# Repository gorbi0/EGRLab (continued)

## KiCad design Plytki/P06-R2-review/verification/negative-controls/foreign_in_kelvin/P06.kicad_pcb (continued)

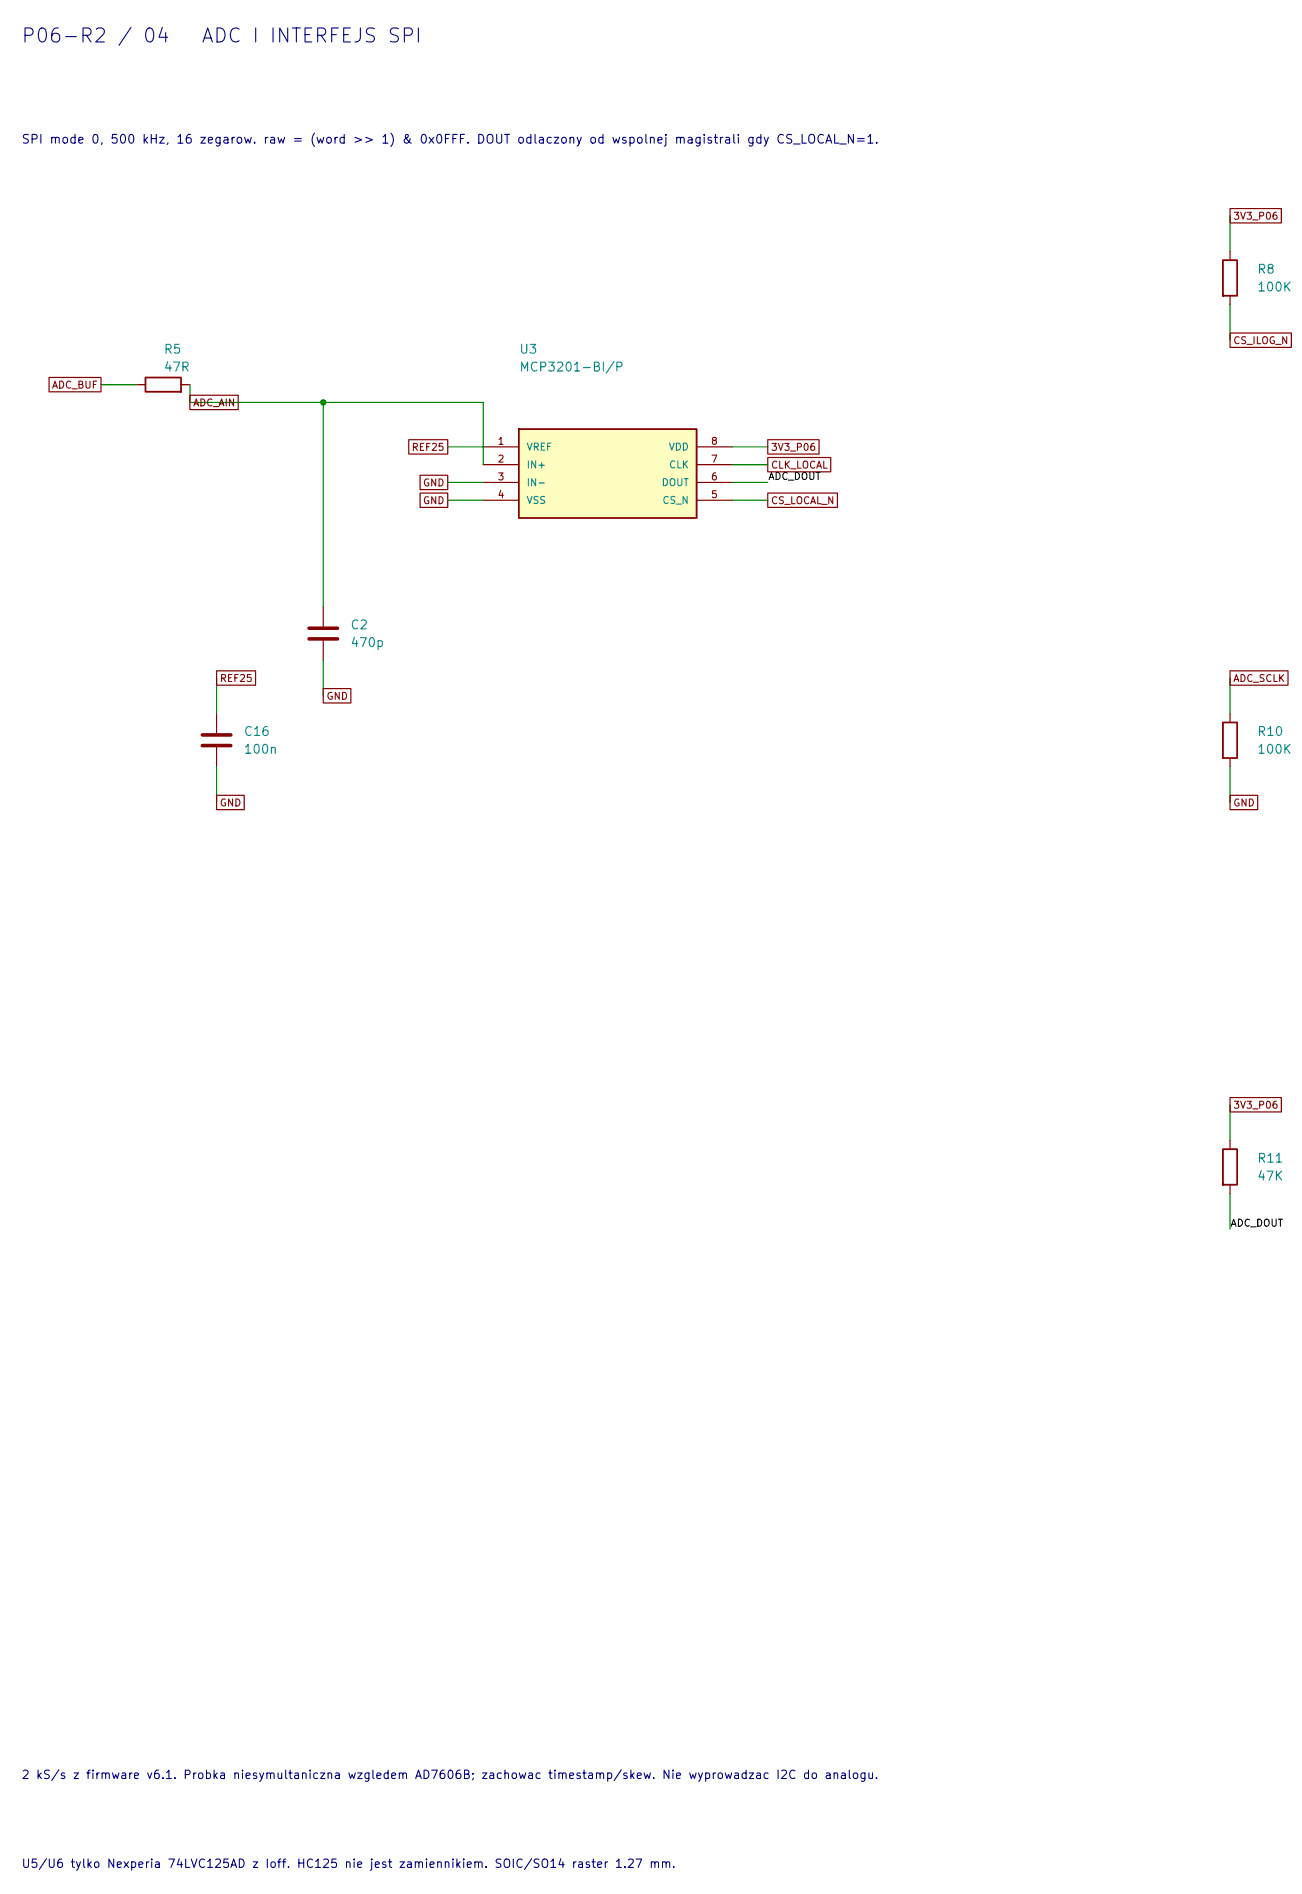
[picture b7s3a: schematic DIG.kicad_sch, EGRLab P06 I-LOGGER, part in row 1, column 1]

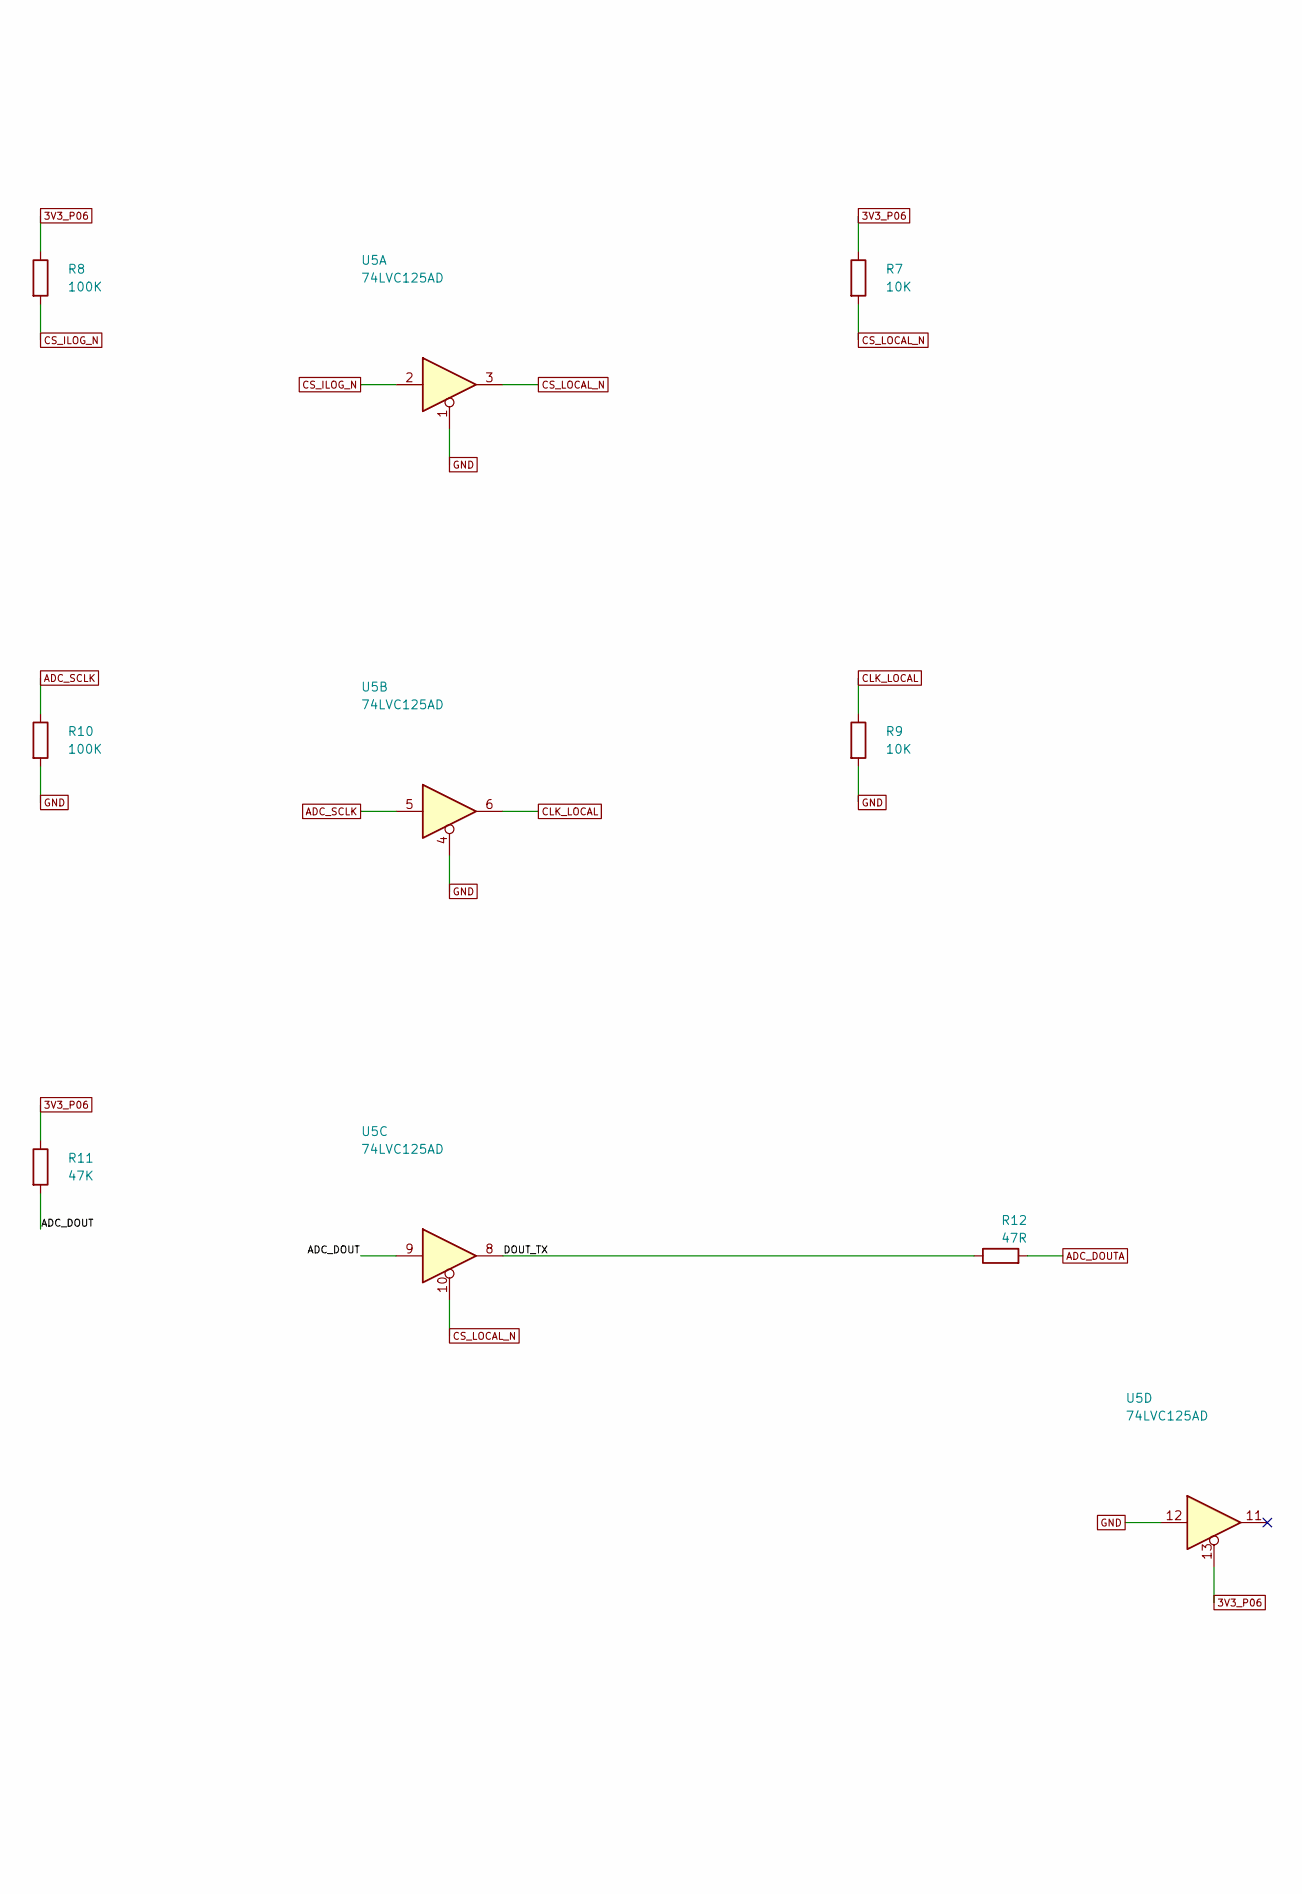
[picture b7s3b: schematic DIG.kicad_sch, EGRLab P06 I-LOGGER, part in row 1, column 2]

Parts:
C2: 470p; C_1206_3216Metric_Pad1.33x1.80mm_HandSolder; MPN SMD 1206 C0G 50V 5% 470p
C16: 100n; C_1206_3216Metric_Pad1.33x1.80mm_HandSolder; MPN SMD 1206 X7R 50V 10% 100n
R5, R12: 47R; R_1206_3216Metric_Pad1.30x1.75mm_HandSolder; MPN RC1206FR-0747RL
R7, R9: 10K; R_1206_3216Metric_Pad1.30x1.75mm_HandSolder; MPN RC1206FR-0710KL
R8, R10: 100K; R_1206_3216Metric_Pad1.30x1.75mm_HandSolder; MPN RC1206FR-07100KL
R11: 47K; R_Axial_DIN0207_L6.3mm_D2.5mm_P5.08mm_Vertical; MPN MF0207FTE-47K (Yageo MF0207 1% 0.6W, ow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
U3: MCP3201-BI/P; DIP-8_W7.62mm; MPN MCP3201-BI/P
U5: 74LVC125AD; SOIC-14_3.9x8.7mm_P1.27mm; MPN 74LVC125AD,118 (Nexperia)

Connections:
3V3_P06: R7.1, R8.1, R11.1, U3.8 (VDD), U5.13; also elsewhere on the board
/DIG/ADC_DOUT: R11.2, U3.6 (DOUT), U5.9
/DIG/DOUT_TX: R12.1, U5.8
ADC_AIN: C2.1, R5.2, U3.2 (IN+); also elsewhere on the board
ADC_BUF: R5.1; also elsewhere on the board
ADC_DOUTA: R12.2; also elsewhere on the board
ADC_SCLK: R10.1, U5.5; also elsewhere on the board
CLK_LOCAL: R9.1, U3.7 (CLK), U5.6; also elsewhere on the board
CS_ILOG_N: R8.2, U5.2; also elsewhere on the board
CS_LOCAL_N: R7.2, U3.5 (CS_N), U5.3, U5.10; also elsewhere on the board
GND: C2.2, C16.2, R9.2, R10.2, U3.3 (IN-), U3.4 (VSS), U5.1, U5.4, U5.12; also elsewhere on the board
REF25: C16.1, U3.1 (VREF); also elsewhere on the board

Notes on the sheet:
SPI mode 0, 500 kHz, 16 zegarow. raw = (word >> 1) & 0x0FFF. DOUT odlaczony od wspolnej magistrali gdy CS_LOCAL_N=1.
2 kS/s z firmware v6.1. Probka niesymultaniczna wzgledem AD7606B; zachowac timestamp/skew. Nie wyprowadzac I2C do analogu.
U5/U6 tylko Nexperia 74LVC125AD z Ioff. HC125 nie jest zamiennikiem. SOIC/SO14 raster 1.27 mm.
P06-R2 / 04 ADC I INTERFEJS SPI

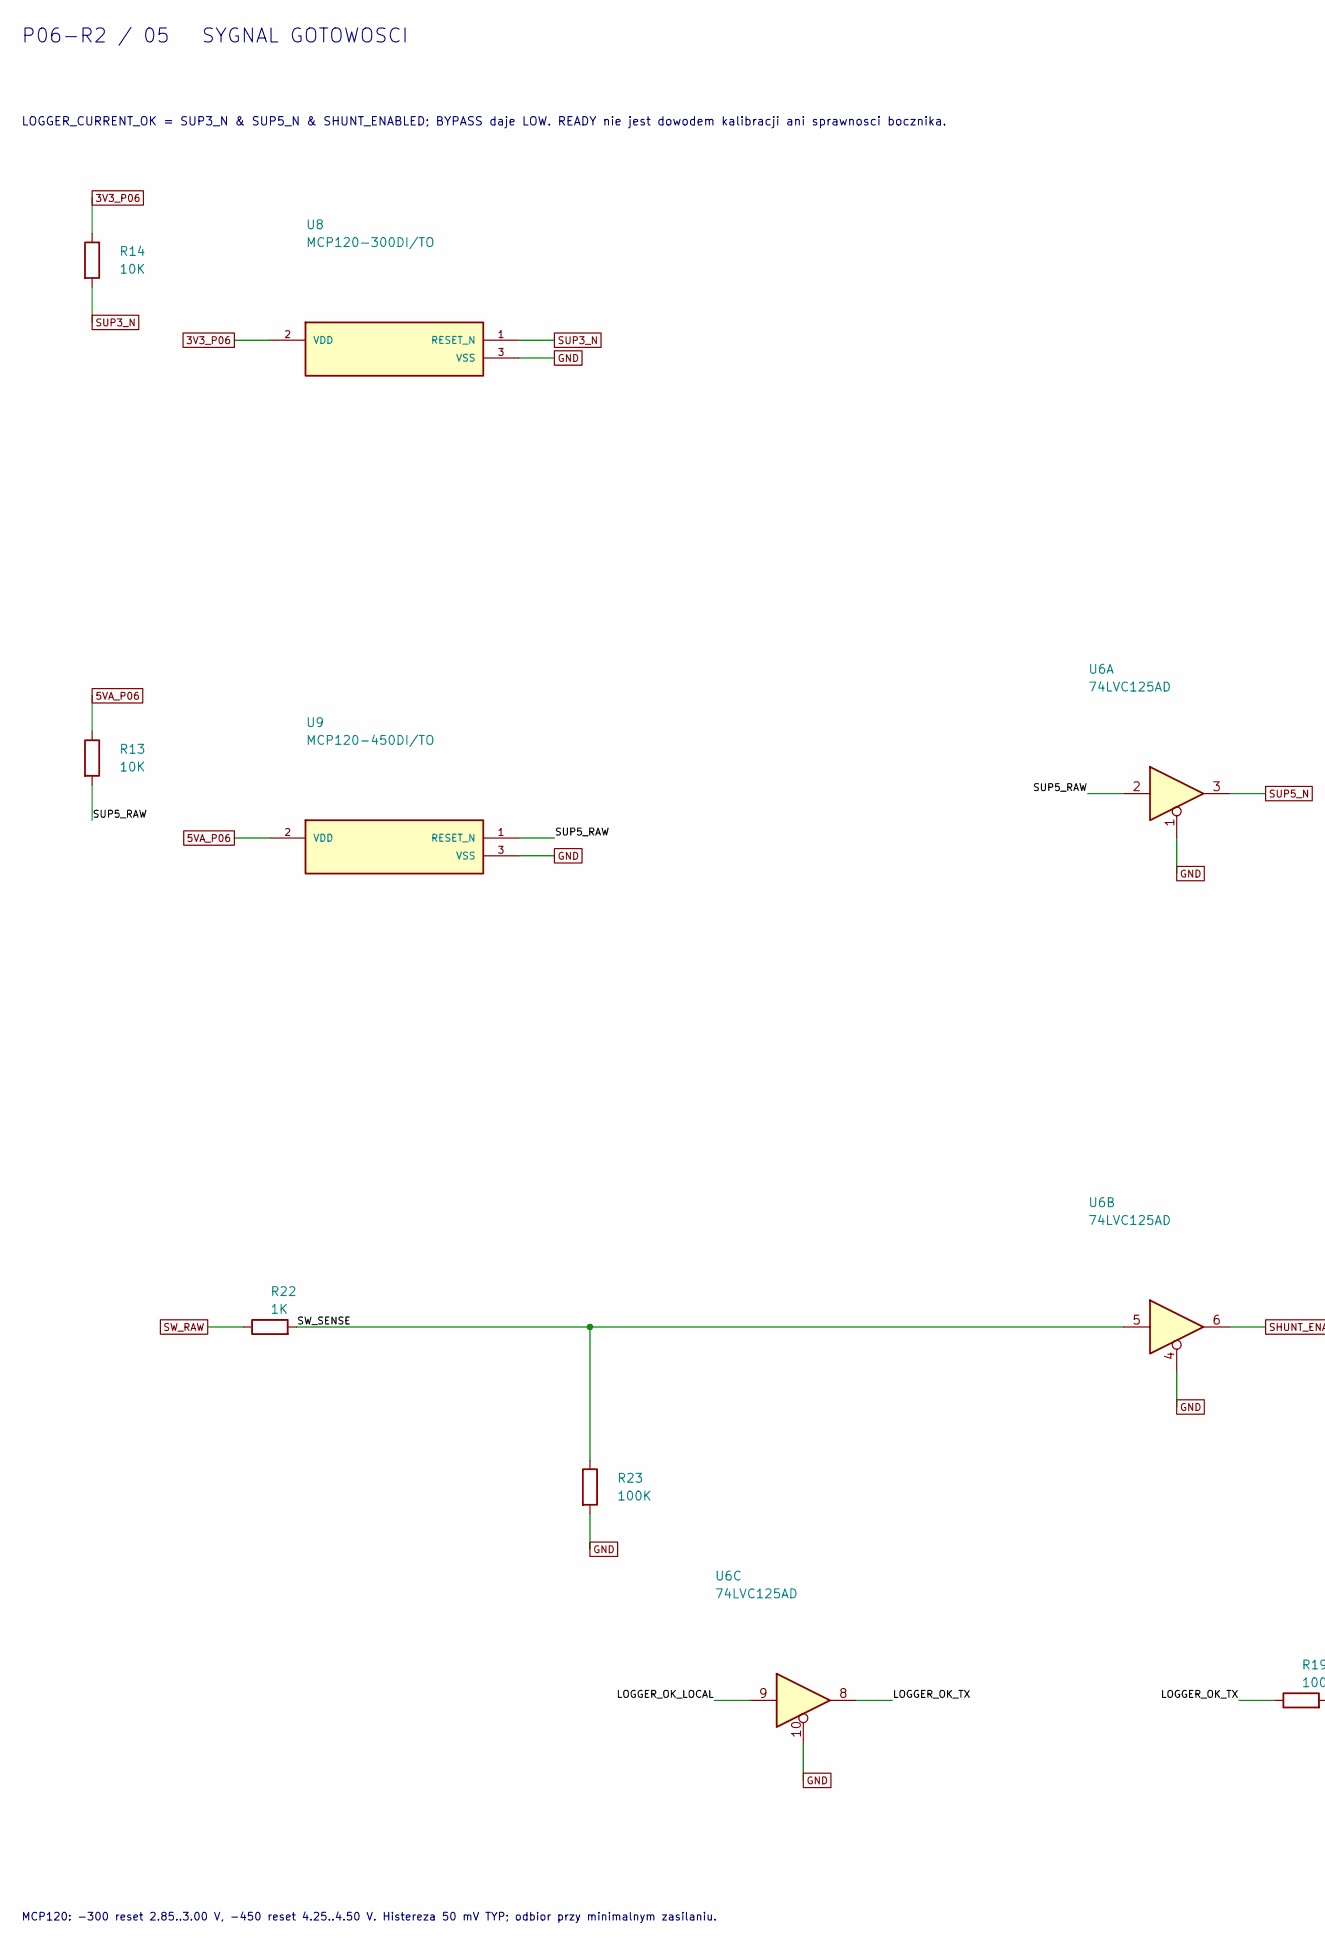
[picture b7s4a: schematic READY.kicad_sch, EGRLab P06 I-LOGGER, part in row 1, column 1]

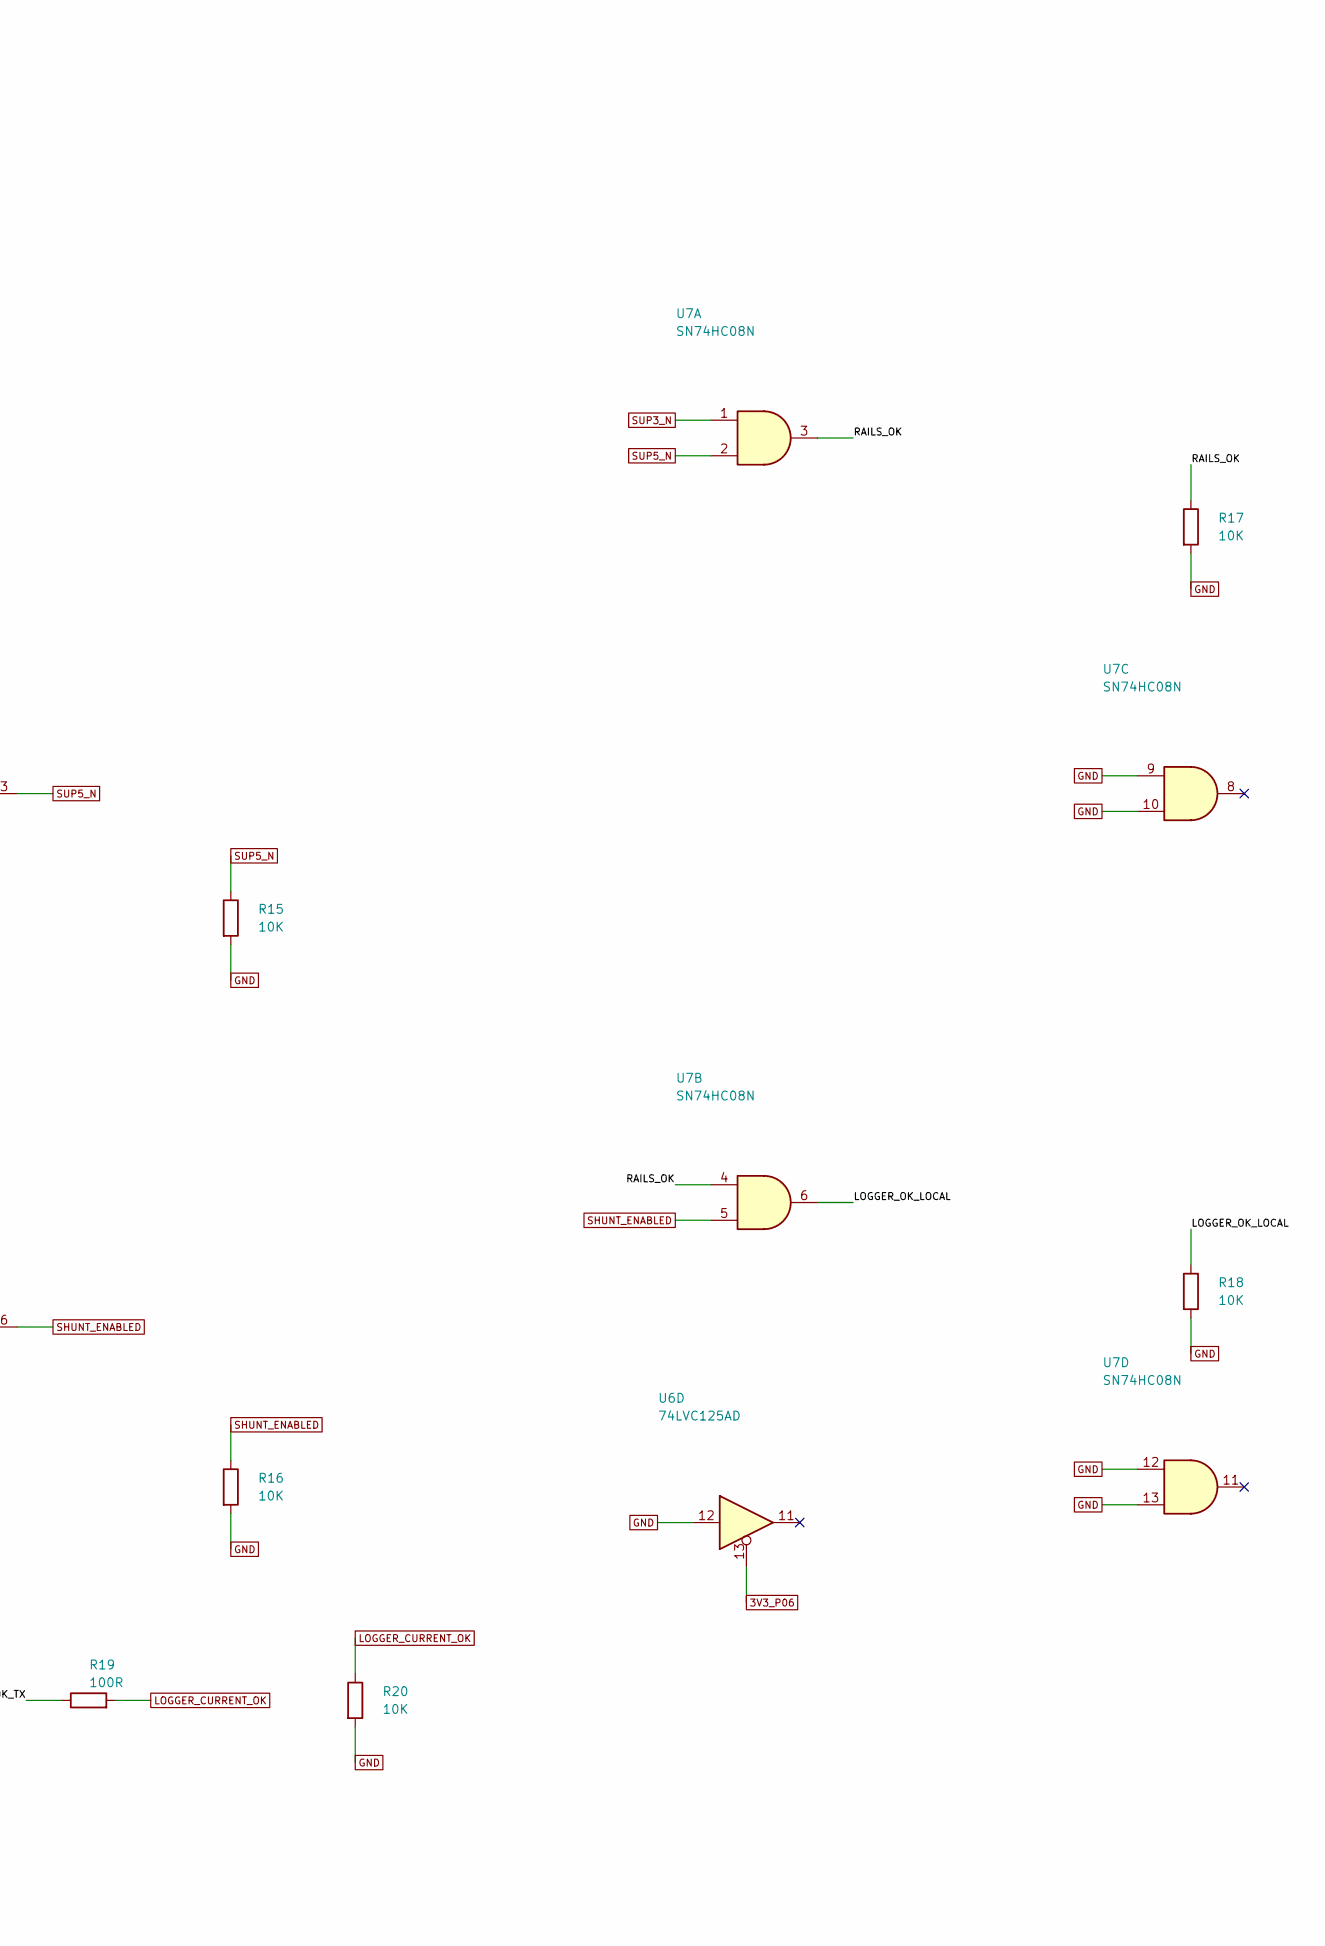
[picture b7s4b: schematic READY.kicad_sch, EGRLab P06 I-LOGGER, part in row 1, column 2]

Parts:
R13, R14, R15, R16, R17, R18, R20: 10K; R_1206_3216Metric_Pad1.30x1.75mm_HandSolder; MPN RC1206FR-0710KL
R19: 100R; R_1206_3216Metric_Pad1.30x1.75mm_HandSolder; MPN RC1206FR-07100RL
R22: 1K; R_1206_3216Metric_Pad1.30x1.75mm_HandSolder; MPN RC1206FR-071KL
R23: 100K; R_1206_3216Metric_Pad1.30x1.75mm_HandSolder; MPN RC1206FR-07100KL
U6: 74LVC125AD; SOIC-14_3.9x8.7mm_P1.27mm; MPN 74LVC125AD,118 (Nexperia)
U7: SN74HC08N; DIP-14_W7.62mm; MPN SN74HC08N
U8: MCP120-300DI/TO; TO-92_Inline_Wide; MPN MCP120-300DI/TO
U9: MCP120-450DI/TO; TO-92_Inline_Wide; MPN MCP120-450DI/TO

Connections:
3V3_P06: R14.1, U6.13, U8.2 (VDD); also elsewhere on the board
5VA_P06: R13.1, U9.2 (VDD); also elsewhere on the board
/READY/LOGGER_OK_LOCAL: R18.1, U6.9, U7.6
/READY/LOGGER_OK_TX: R19.1, U6.8
/READY/RAILS_OK: R17.1, U7.3, U7.4
/READY/SUP5_RAW: R13.2, U6.2, U9.1 (RESET_N)
/READY/SW_SENSE: R22.2, R23.1, U6.5
GND: R15.2, R16.2, R17.2, R18.2, R20.2, R23.2, U6.1, U6.4, U6.10, U6.12, U7.9, U7.10, U7.12, U7.13, U8.3 (VSS), U9.3 (VSS); also elsewhere on the board
LOGGER_CURRENT_OK: R19.2, R20.1; also elsewhere on the board
SHUNT_ENABLED: R16.1, U6.6, U7.5; also elsewhere on the board
SUP3_N: R14.2, U7.1, U8.1 (RESET_N); also elsewhere on the board
SUP5_N: R15.1, U6.3, U7.2; also elsewhere on the board
SW_RAW: R22.1; also elsewhere on the board

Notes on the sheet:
LOGGER_CURRENT_OK = SUP3_N & SUP5_N & SHUNT_ENABLED; BYPASS daje LOW. READY nie jest dowodem kalibracji ani sprawnosci bocznika.
MCP120: -300 reset 2.85..3.00 V, -450 reset 4.25..4.50 V. Histereza 50 mV TYP; odbior przy minimalnym zasilaniu.
P06-R2 / 05 SYGNAL GOTOWOSCI

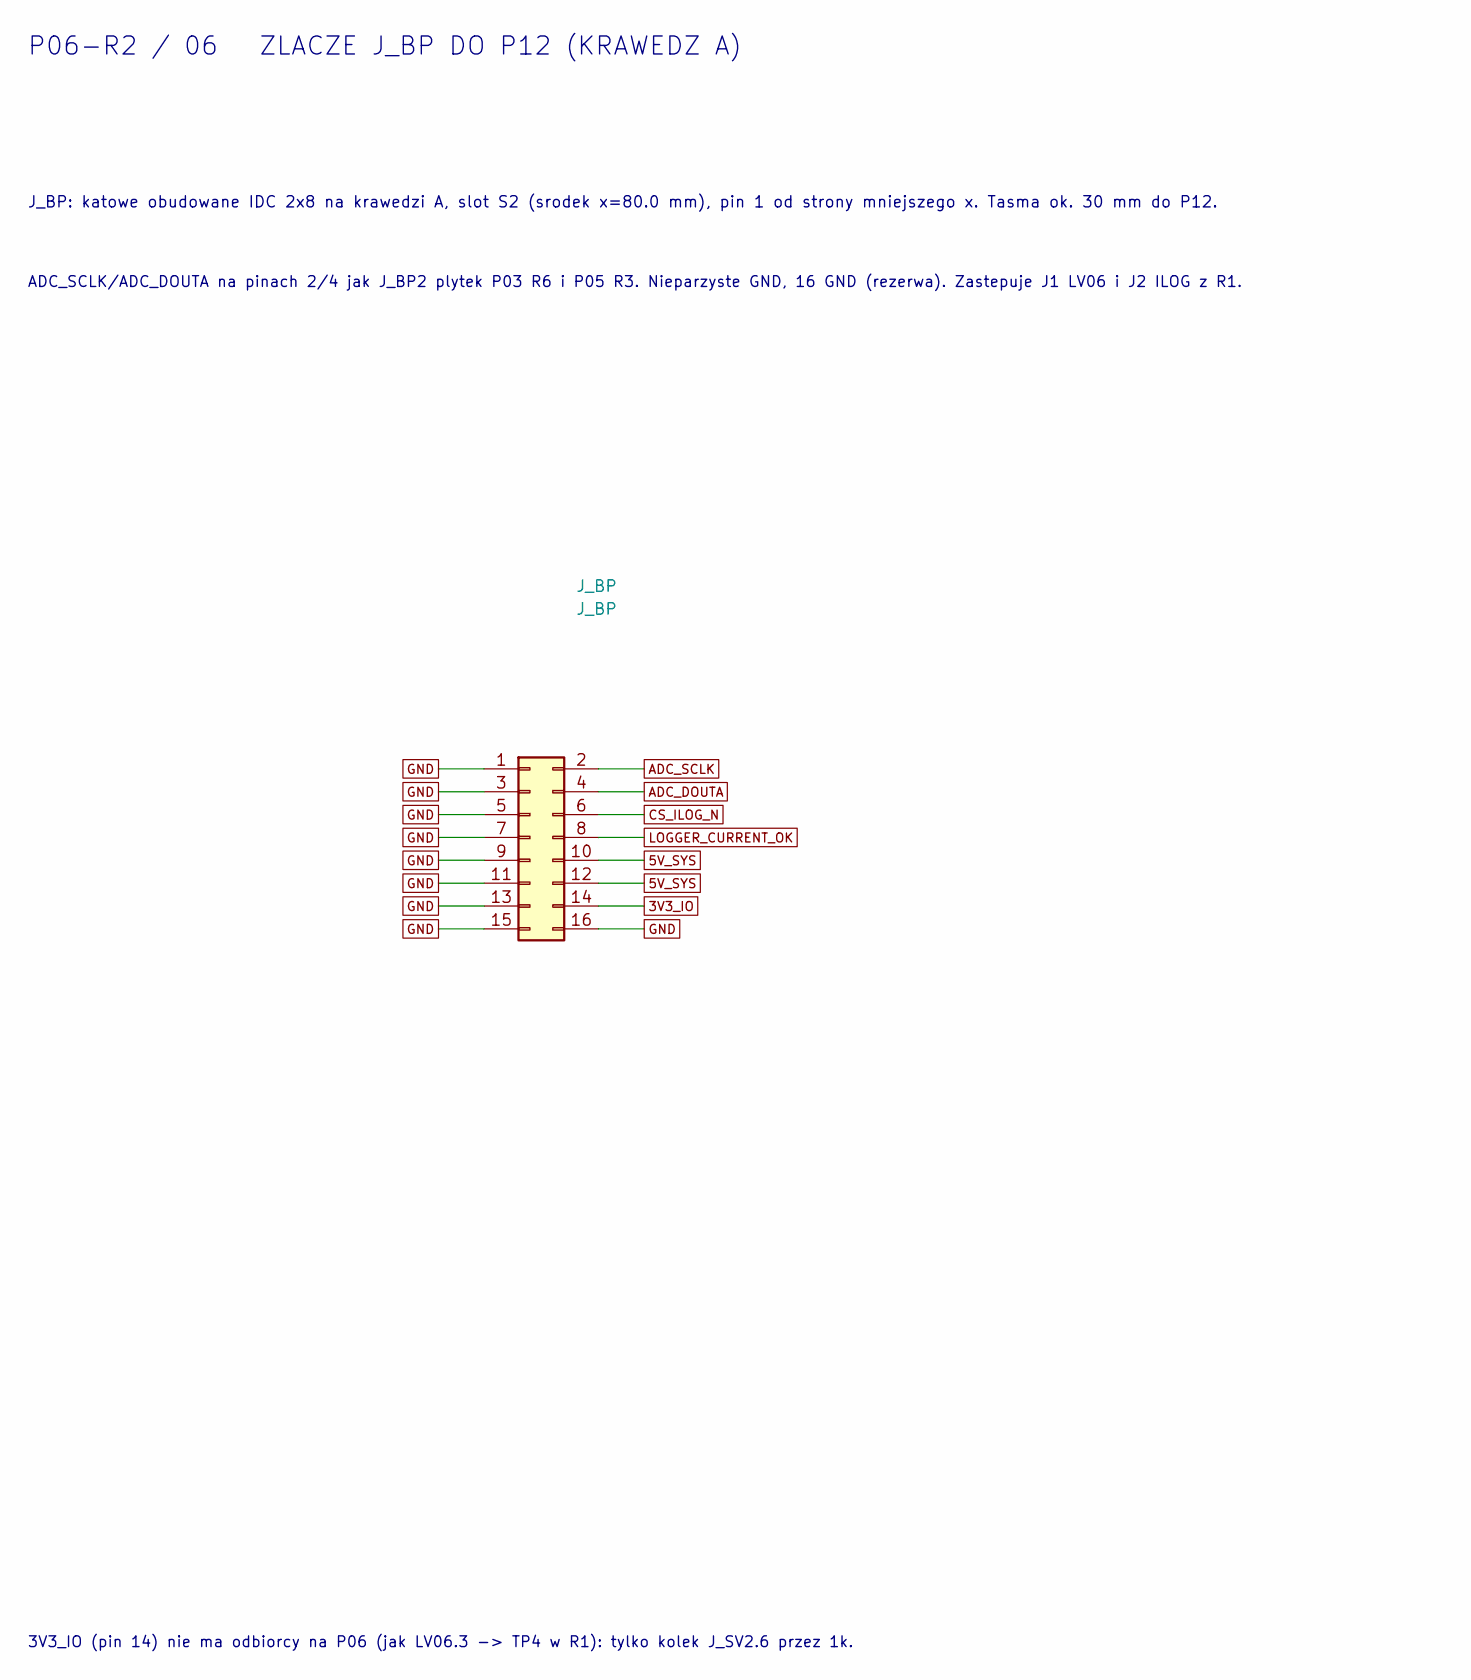
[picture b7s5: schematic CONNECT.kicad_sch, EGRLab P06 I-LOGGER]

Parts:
J_BP: J_BP; IDC-Header_2x08_P2.54mm_Horizontal; MPN IDC header 2x8 2.54mm angled shrouded, 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

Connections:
3V3_IO: J_BP.14; also elsewhere on the board
5V_SYS: J_BP.10, J_BP.12; also elsewhere on the board
ADC_DOUTA: J_BP.4; also elsewhere on the board
ADC_SCLK: J_BP.2; also elsewhere on the board
CS_ILOG_N: J_BP.6; also elsewhere on the board
GND: J_BP.1, J_BP.3, J_BP.5, J_BP.7, J_BP.9, J_BP.11, J_BP.13, J_BP.15, J_BP.16; also elsewhere on the board
LOGGER_CURRENT_OK: J_BP.8; also elsewhere on the board

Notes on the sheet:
J_BP: katowe obudowane IDC 2x8 na krawedzi A, slot S2 (srodek x=80.0 mm), pin 1 od strony mniejszego x. Tasma ok. 30 mm do P12.
ADC_SCLK/ADC_DOUTA na pinach 2/4 jak J_BP2 plytek P03 R6 i P05 R3. Nieparzyste GND, 16 GND (rezerwa). Zastepuje J1 LV06 i J2 ILOG z R1.
3V3_IO (pin 14) nie ma odbiorcy na P06 (jak LV06.3 -> TP4 w R1): tylko kolek J_SV2.6 przez 1k.
P06-R2 / 06 ZLACZE J_BP DO P12 (KRAWEDZ A)

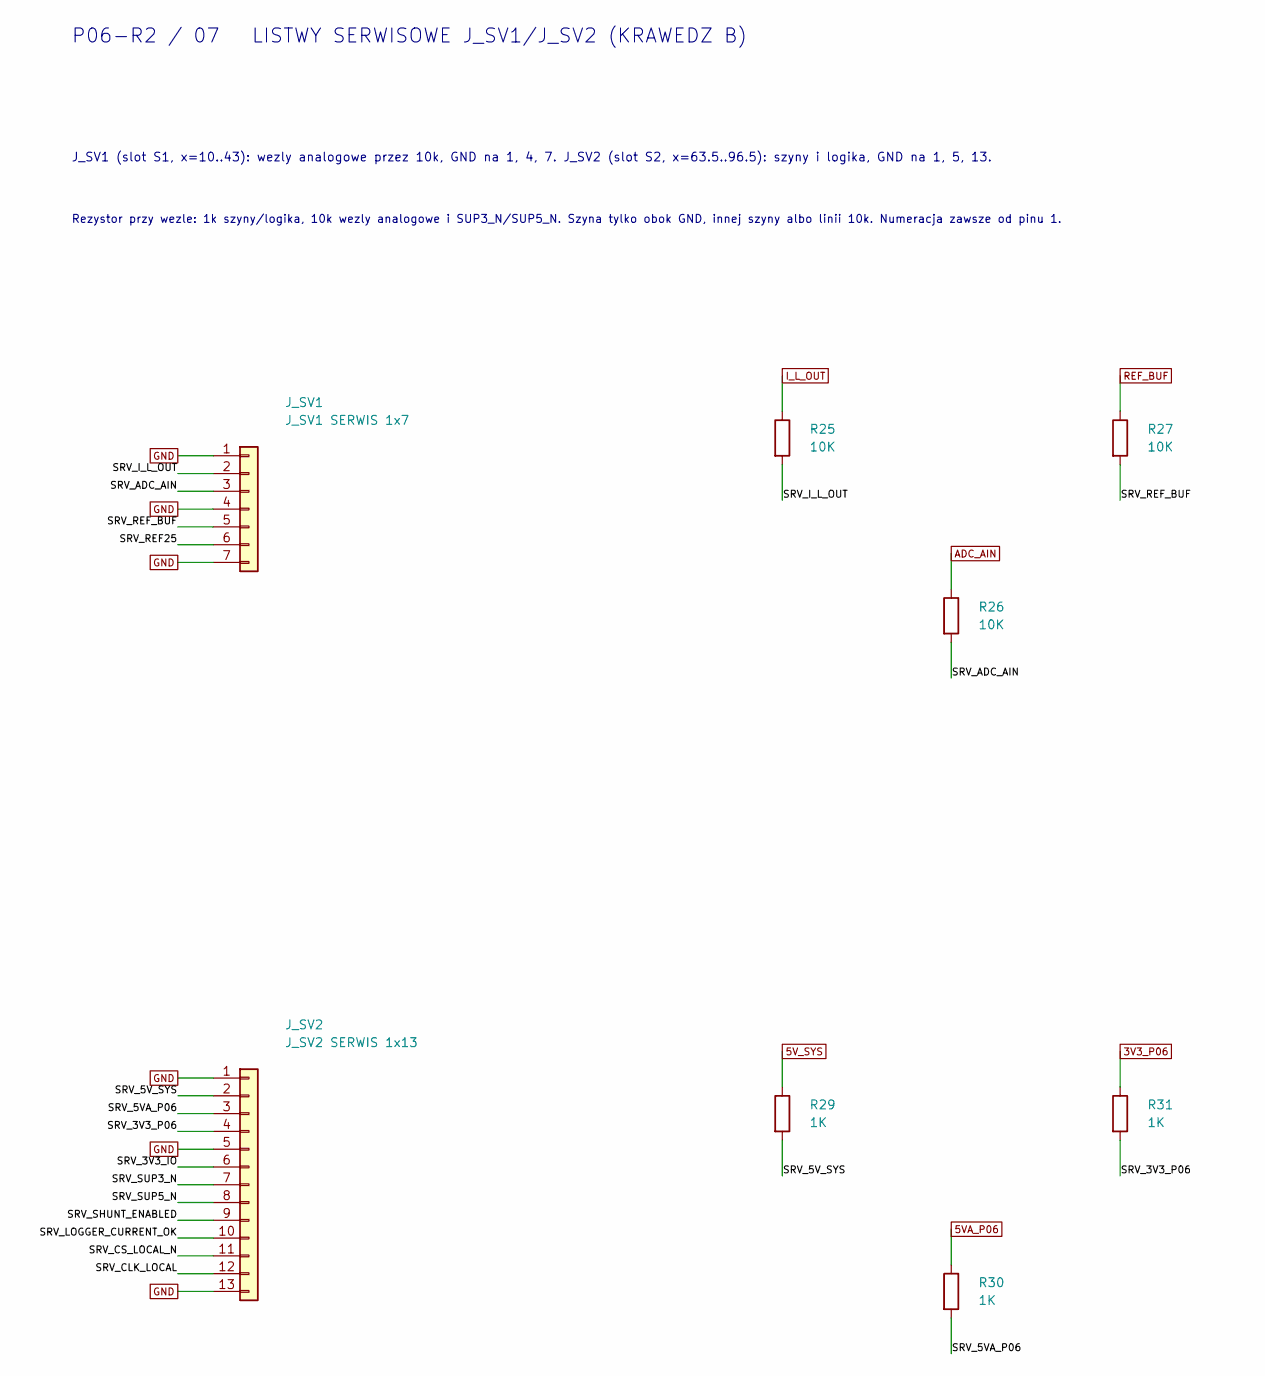
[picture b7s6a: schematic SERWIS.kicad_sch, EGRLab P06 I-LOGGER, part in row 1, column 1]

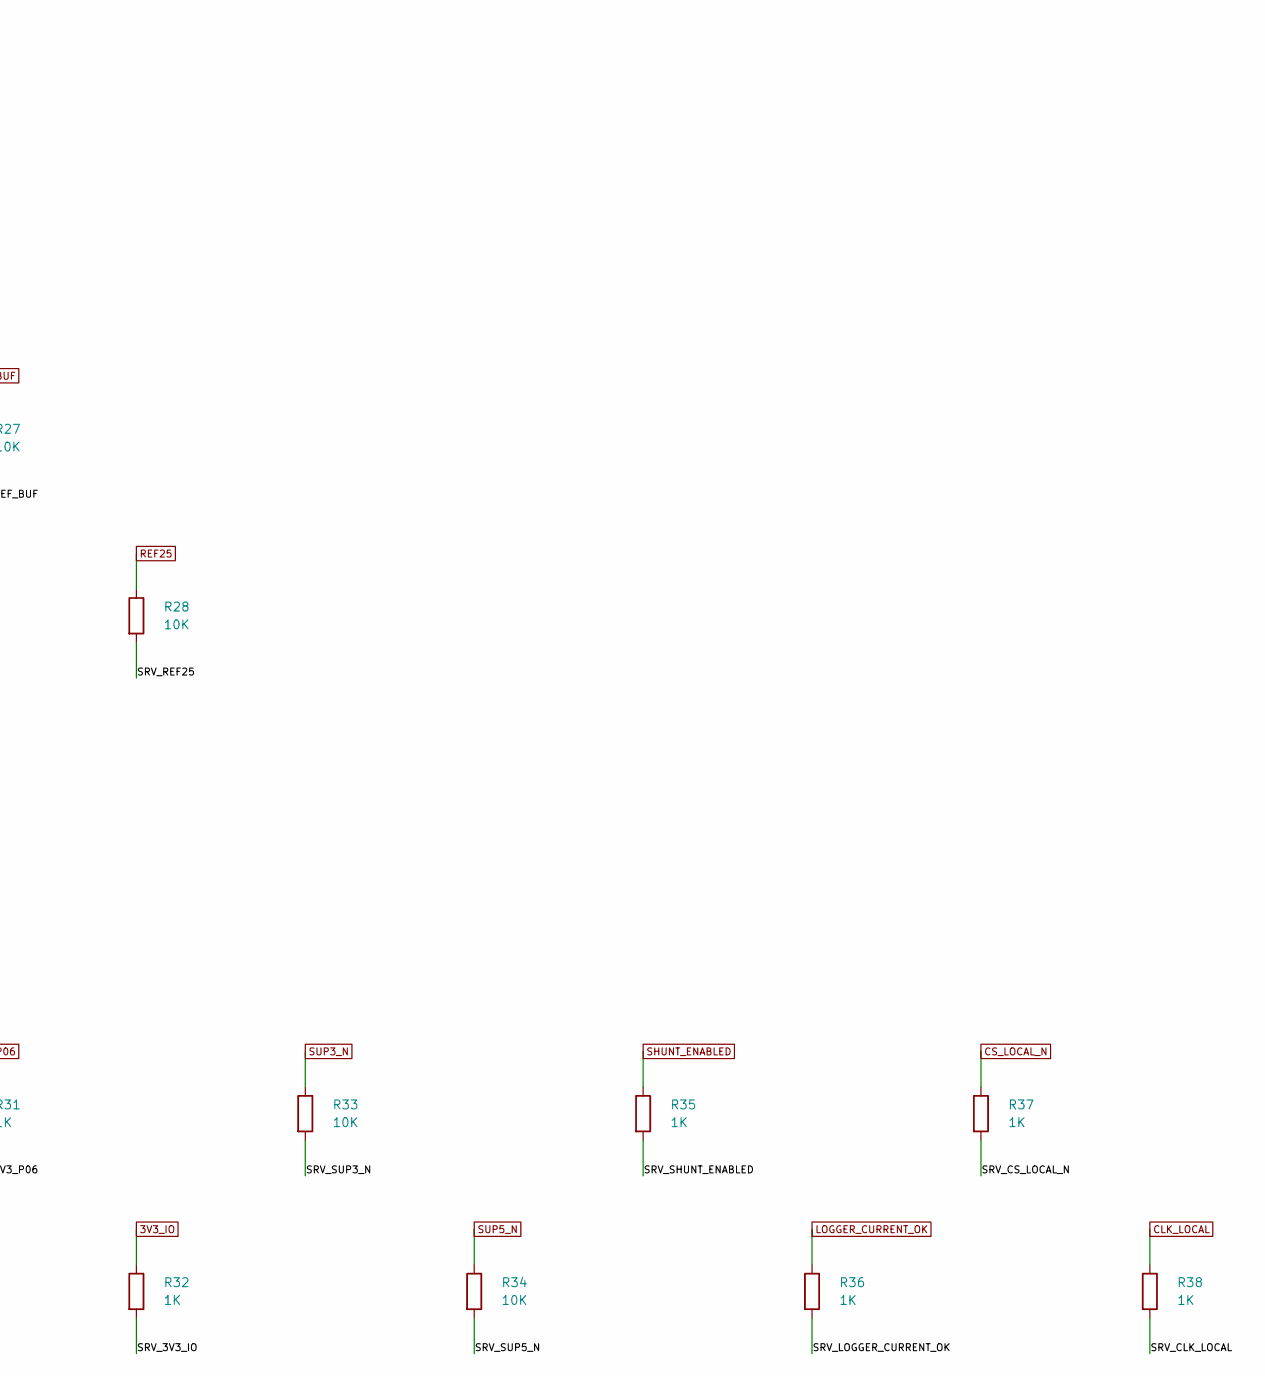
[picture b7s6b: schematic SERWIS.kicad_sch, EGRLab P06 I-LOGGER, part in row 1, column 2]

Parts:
J_SV1: J_SV1 SERWIS 1x7; PinHeader_1x07_P2.54mm_Horizontal; MPN Pin header 1x7, 2.54 mm, right angle, Au
J_SV2: J_SV2 SERWIS 1x13; PinHeader_1x13_P2.54mm_Horizontal; MPN Pin header 1x13, 2.54 mm, right angle, 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
R25, R26, R27, R28, R33, R34: 10K; R_1206_3216Metric_Pad1.30x1.75mm_HandSolder; MPN RC1206FR-0710KL
R29, R30, R31, R32, R35, R36, R37, R38: 1K; R_1206_3216Metric_Pad1.30x1.75mm_HandSolder; MPN RC1206FR-071KL

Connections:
3V3_IO: R32.1; also elsewhere on the board
3V3_P06: R31.1; also elsewhere on the board
5VA_P06: R30.1; also elsewhere on the board
5V_SYS: R29.1; also elsewhere on the board
/SERWIS/SRV_3V3_IO: J_SV2.6, R32.2
/SERWIS/SRV_3V3_P06: J_SV2.4, R31.2
/SERWIS/SRV_5VA_P06: J_SV2.3, R30.2
/SERWIS/SRV_5V_SYS: J_SV2.2, R29.2
/SERWIS/SRV_ADC_AIN: J_SV1.3, R26.2
/SERWIS/SRV_CLK_LOCAL: J_SV2.12, R38.2
/SERWIS/SRV_CS_LOCAL_N: J_SV2.11, R37.2
/SERWIS/SRV_I_L_OUT: J_SV1.2, R25.2
/SERWIS/SRV_LOGGER_CURRENT_OK: J_SV2.10, R36.2
/SERWIS/SRV_REF25: J_SV1.6, R28.2
/SERWIS/SRV_REF_BUF: J_SV1.5, R27.2
/SERWIS/SRV_SHUNT_ENABLED: J_SV2.9, R35.2
/SERWIS/SRV_SUP3_N: J_SV2.7, R33.2
/SERWIS/SRV_SUP5_N: J_SV2.8, R34.2
ADC_AIN: R26.1; also elsewhere on the board
CLK_LOCAL: R38.1; also elsewhere on the board
CS_LOCAL_N: R37.1; also elsewhere on the board
GND: J_SV1.1, J_SV1.4, J_SV1.7, J_SV2.1, J_SV2.5, J_SV2.13; also elsewhere on the board
I_L_OUT: R25.1; also elsewhere on the board
LOGGER_CURRENT_OK: R36.1; also elsewhere on the board
REF25: R28.1; also elsewhere on the board
REF_BUF: R27.1; also elsewhere on the board
SHUNT_ENABLED: R35.1; also elsewhere on the board
SUP3_N: R33.1; also elsewhere on the board
SUP5_N: R34.1; also elsewhere on the board

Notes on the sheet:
J_SV1 (slot S1, x=10..43): wezly analogowe przez 10k, GND na 1, 4, 7. J_SV2 (slot S2, x=63.5..96.5): szyny i logika, GND na 1, 5, 13.
Rezystor przy wezle: 1k szyny/logika, 10k wezly analogowe i SUP3_N/SUP5_N. Szyna tylko obok GND, innej szyny albo linii 10k. Numeracja zawsze od pinu 1.
P06-R2 / 07 LISTWY SERWISOWE J_SV1/J_SV2 (KRAWEDZ B)
